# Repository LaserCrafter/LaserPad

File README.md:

# LaserPad
 Open Source replacement PCB for the Lightpad v2

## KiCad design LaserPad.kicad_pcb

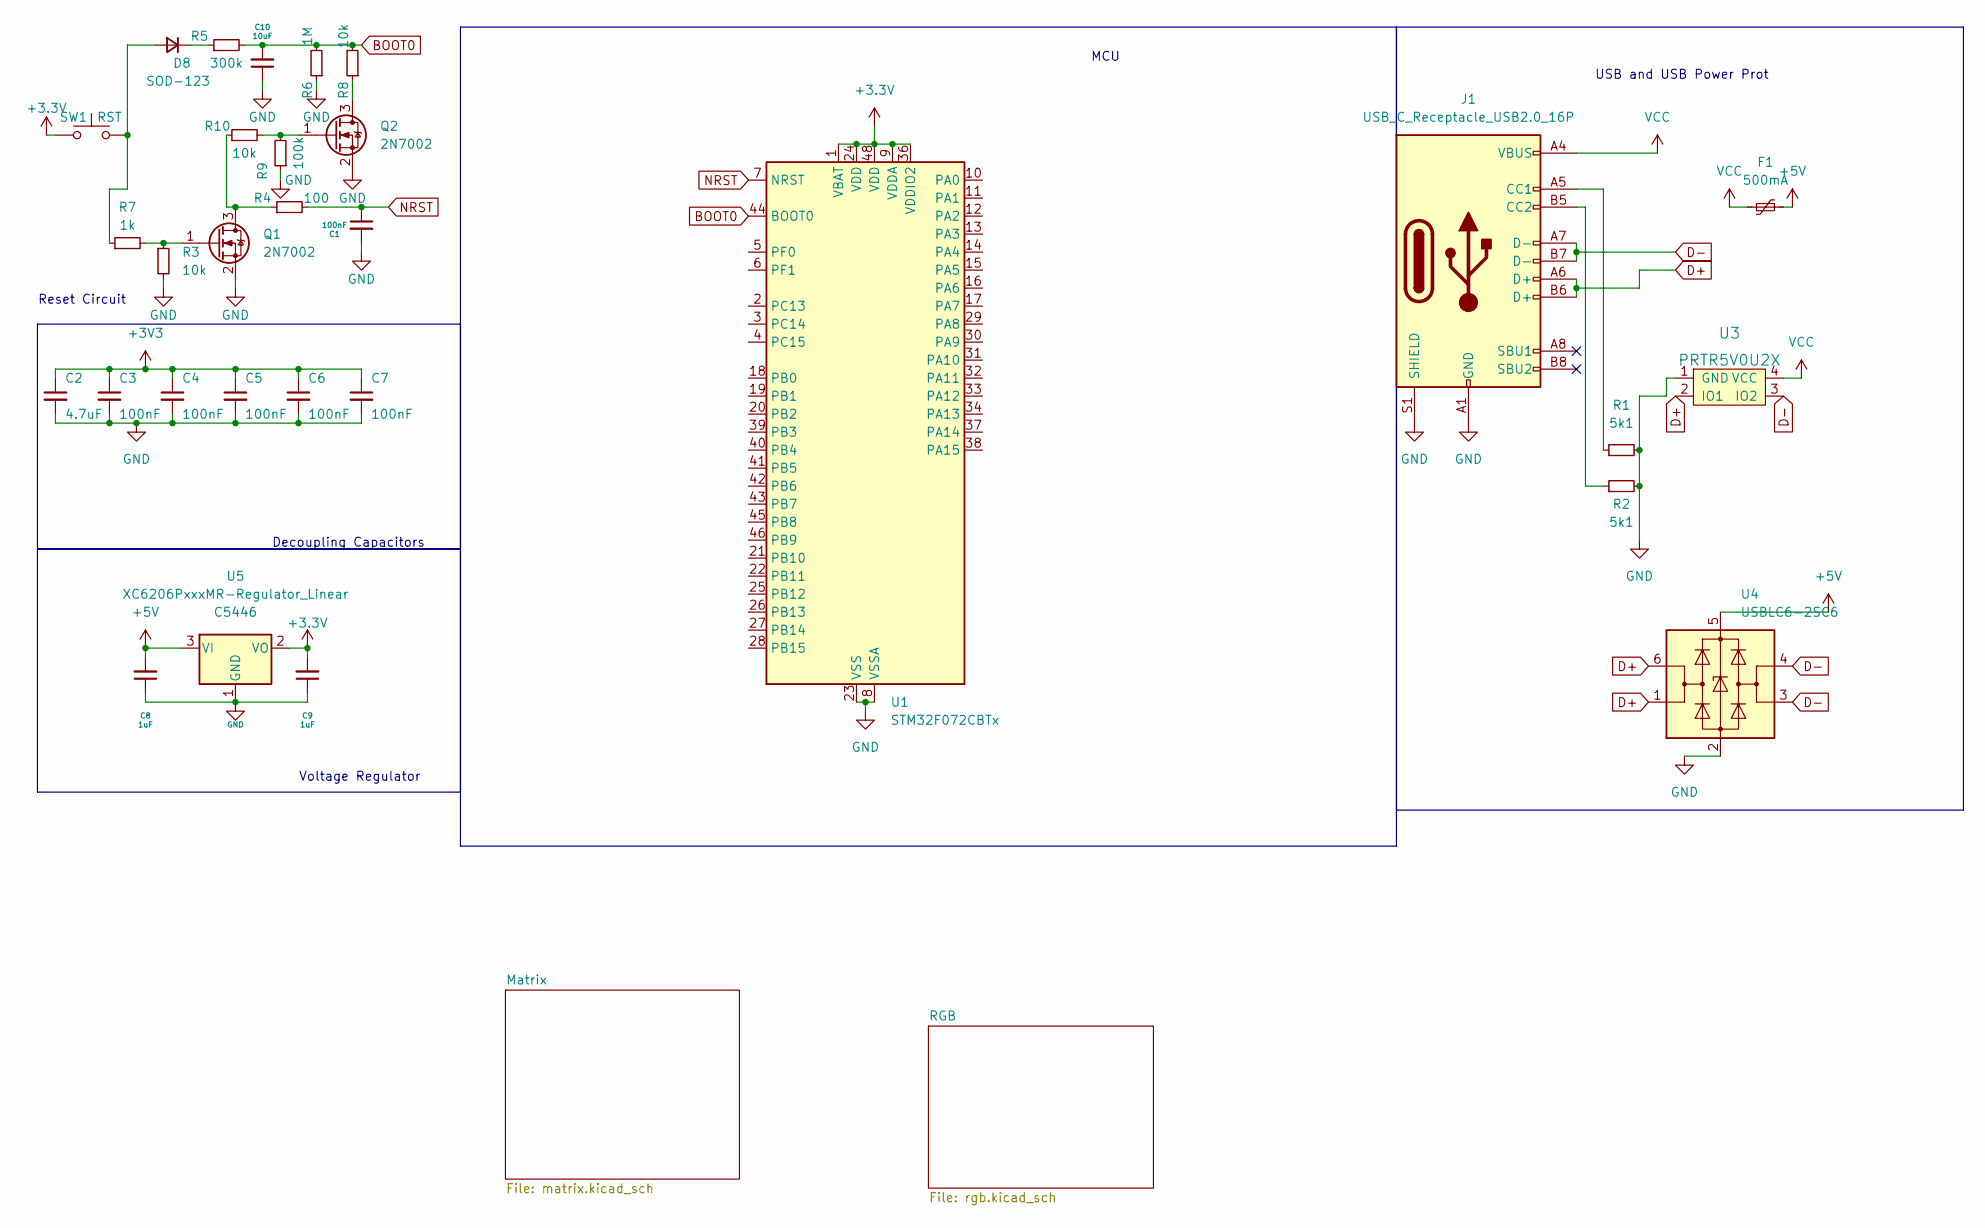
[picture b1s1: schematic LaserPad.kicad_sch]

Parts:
C1: 100nF; C_0402_1005Metric; LCSC C52923
C2: 4.7uF; C_0402_1005Metric; LCSC C52923
C3, C4, C5, C6, C7: 100nF; C_0402_1005Metric; LCSC C307331
C8, C9: 1uF; C_0402_1005Metric; LCSC C52923
C10: 10uF; C_0402_1005Metric; LCSC C52923
D8: SOD-123; D_SOD-123
F1: 500mA; Fuse_1206_3216Metric
J1: USB_C_Receptacle_USB2.0_16P; USB_C_Receptacle_HRO_TYPE-C-31-M-12
Q1, Q2: 2N7002; SOT-23
R1, R2: 5k1; R_0402_1005Metric
R3, R8, R10: 10k; R_0402_1005Metric
R4: 100; R_0402_1005Metric
R5: 300k; R_0402_1005Metric
R6: 1M; R_0402_1005Metric
R7: 1k; R_0402_1005Metric
R9: 100k; R_0402_1005Metric
SW1: RST; SW_SPST_SKQG_WithoutStem
U1: STM32F072CBTx; LQFP-48_7x7mm_P0.5mm
U3: PRTR5V0U2X; SOT143B
U4: USBLC6-2SC6; SOT-23-6
U5: XC6206PxxxMR-Regulator_Linear; SOT-23; LCSC C5446

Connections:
+3.3V: C9.2, SW1.1, U1.1 (VBAT), U1.9 (VDDA), U1.24 (VDD), U1.36 (VDDIO2), U1.48 (VDD), U5.2 (VO)
+3V3: C2.1, C3.1, C4.1, C5.1, C6.1, C7.1
+5V: C8.2, F1.1, F1.2, J1.A4 (VBUS), J1.A9 (VBUS), J1.B4 (VBUS), J1.B9 (VBUS), U3.4 (VCC), U4.5 (VBUS), U5.3 (VI); also elsewhere on the board
BOOT0: C10.2, R5.2, R6.2, R8.2, U1.44 (BOOT0)
D+: J1.A6 (D+), J1.B6 (D+), U3.2 (IO1), U4.1 (I/O1), U4.6 (I/O1)
D-: J1.A7 (D-), J1.B7 (D-), U3.3 (IO2), U4.3 (I/O2), U4.4 (I/O2)
GND: C1.2, C2.2, C3.2, C4.2, C5.2, C6.2, C7.2, C8.1, C9.1, C10.1, J1.A1 (GND), J1.A12 (GND), J1.B1 (GND), J1.B12 (GND), J1.S1 (SHIELD), Q1.2 (S), Q2.2 (S), R1.2, R2.2, R3.2, R6.1, R9.1, U1.8 (VSSA), U1.23 (VSS), U1.35 (VSS), U1.47 (VSS), U3.1 (GND), U4.2 (GND), U5.1 (GND); also elsewhere on the board
NRST: C1.1, R4.2, U1.7 (NRST)
unnamed: D8.2 (A), R7.1, SW1.2
unnamed: D8.1 (K), R5.1
unnamed: J1.A5 (CC1), R1.1
unnamed: J1.B5 (CC2), R2.1
unnamed: Q1.3 (D), R4.1, R10.1
unnamed: Q1.1 (G), R3.1, R7.2
unnamed: Q2.3 (D), R8.1
unnamed: Q2.1 (G), R9.2, R10.2

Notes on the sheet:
Voltage Regulator
MCU
Decoupling Capacitors
Reset Circuit
USB and USB Power Prot

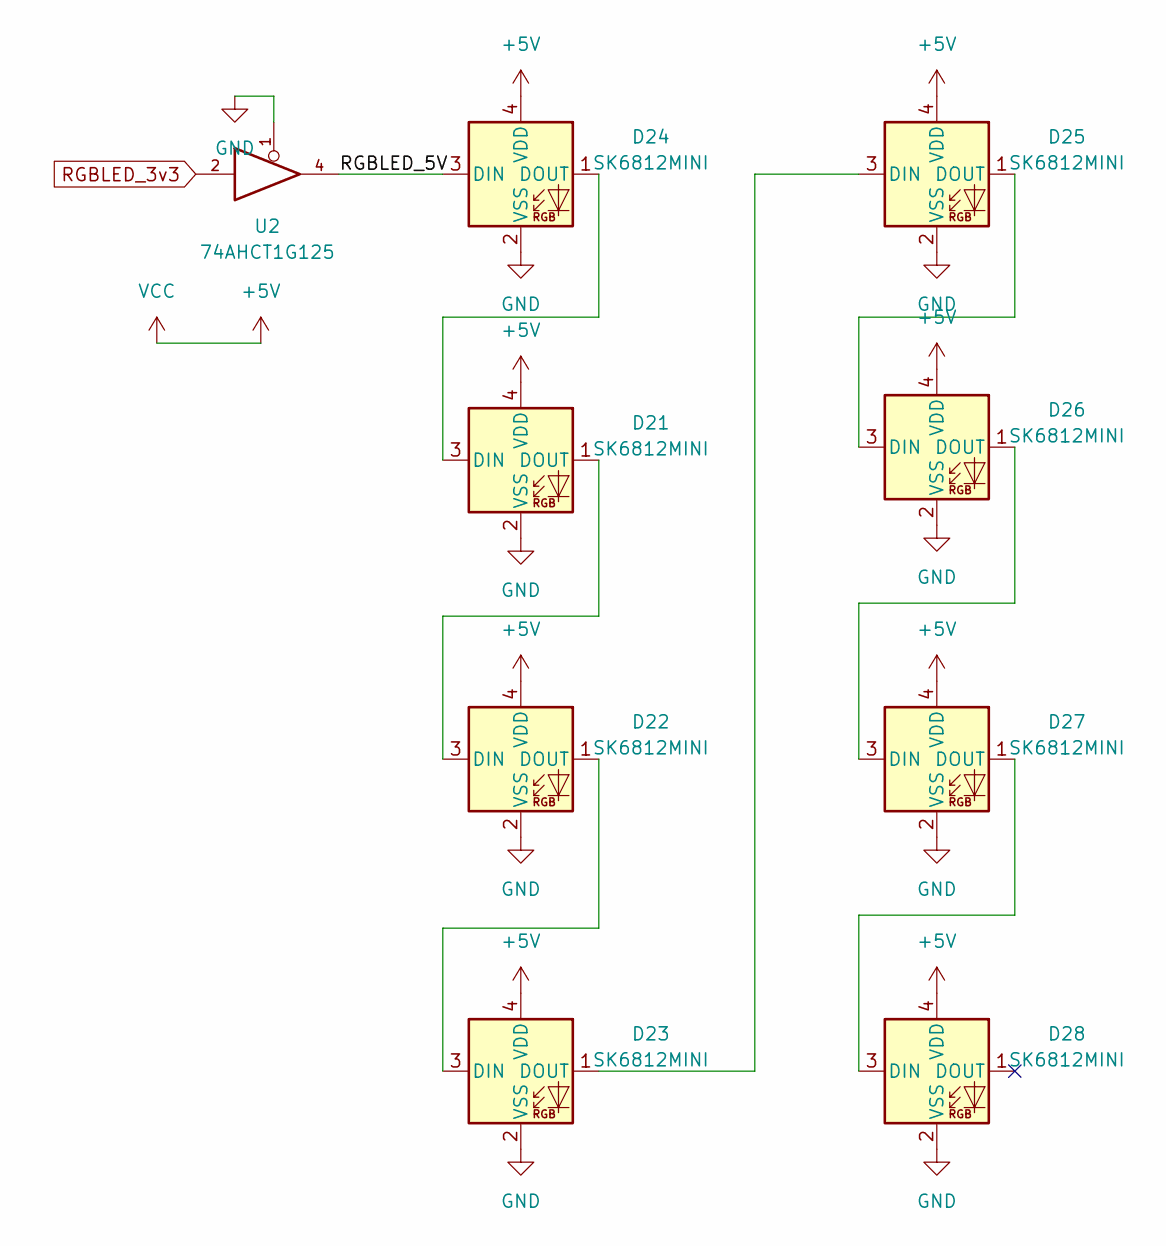
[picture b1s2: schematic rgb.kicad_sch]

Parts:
D21, D22, D23, D24, D25, D26, D27, D28: SK6812MINI; LED_SK6812MINI_PLCC4_3.5x3.5mm_P1.75mm
U2: 74AHCT1G125; SOT-23-5

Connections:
+5V: D21.4 (VDD), D22.4 (VDD), D23.4 (VDD), D24.4 (VDD), D25.4 (VDD), D26.4 (VDD), D27.4 (VDD), D28.4 (VDD), U2.5 (VCC); also elsewhere on the board
/RGB/RGBLED_5V: D24.3 (DIN), U2.4
GND: D21.2 (VSS), D22.2 (VSS), D23.2 (VSS), D24.2 (VSS), D25.2 (VSS), D26.2 (VSS), D27.2 (VSS), D28.2 (VSS), U2.1, U2.3 (GND); also elsewhere on the board
unnamed: D21.3 (DIN), D24.1 (DOUT)
unnamed: D21.1 (DOUT), D22.3 (DIN)
unnamed: D22.1 (DOUT), D23.3 (DIN)
unnamed: D23.1 (DOUT), D25.3 (DIN)
unnamed: D25.1 (DOUT), D26.3 (DIN)
unnamed: D26.1 (DOUT), D27.3 (DIN)
unnamed: D27.1 (DOUT), D28.3 (DIN)
RGBLED_3v3: U2.2

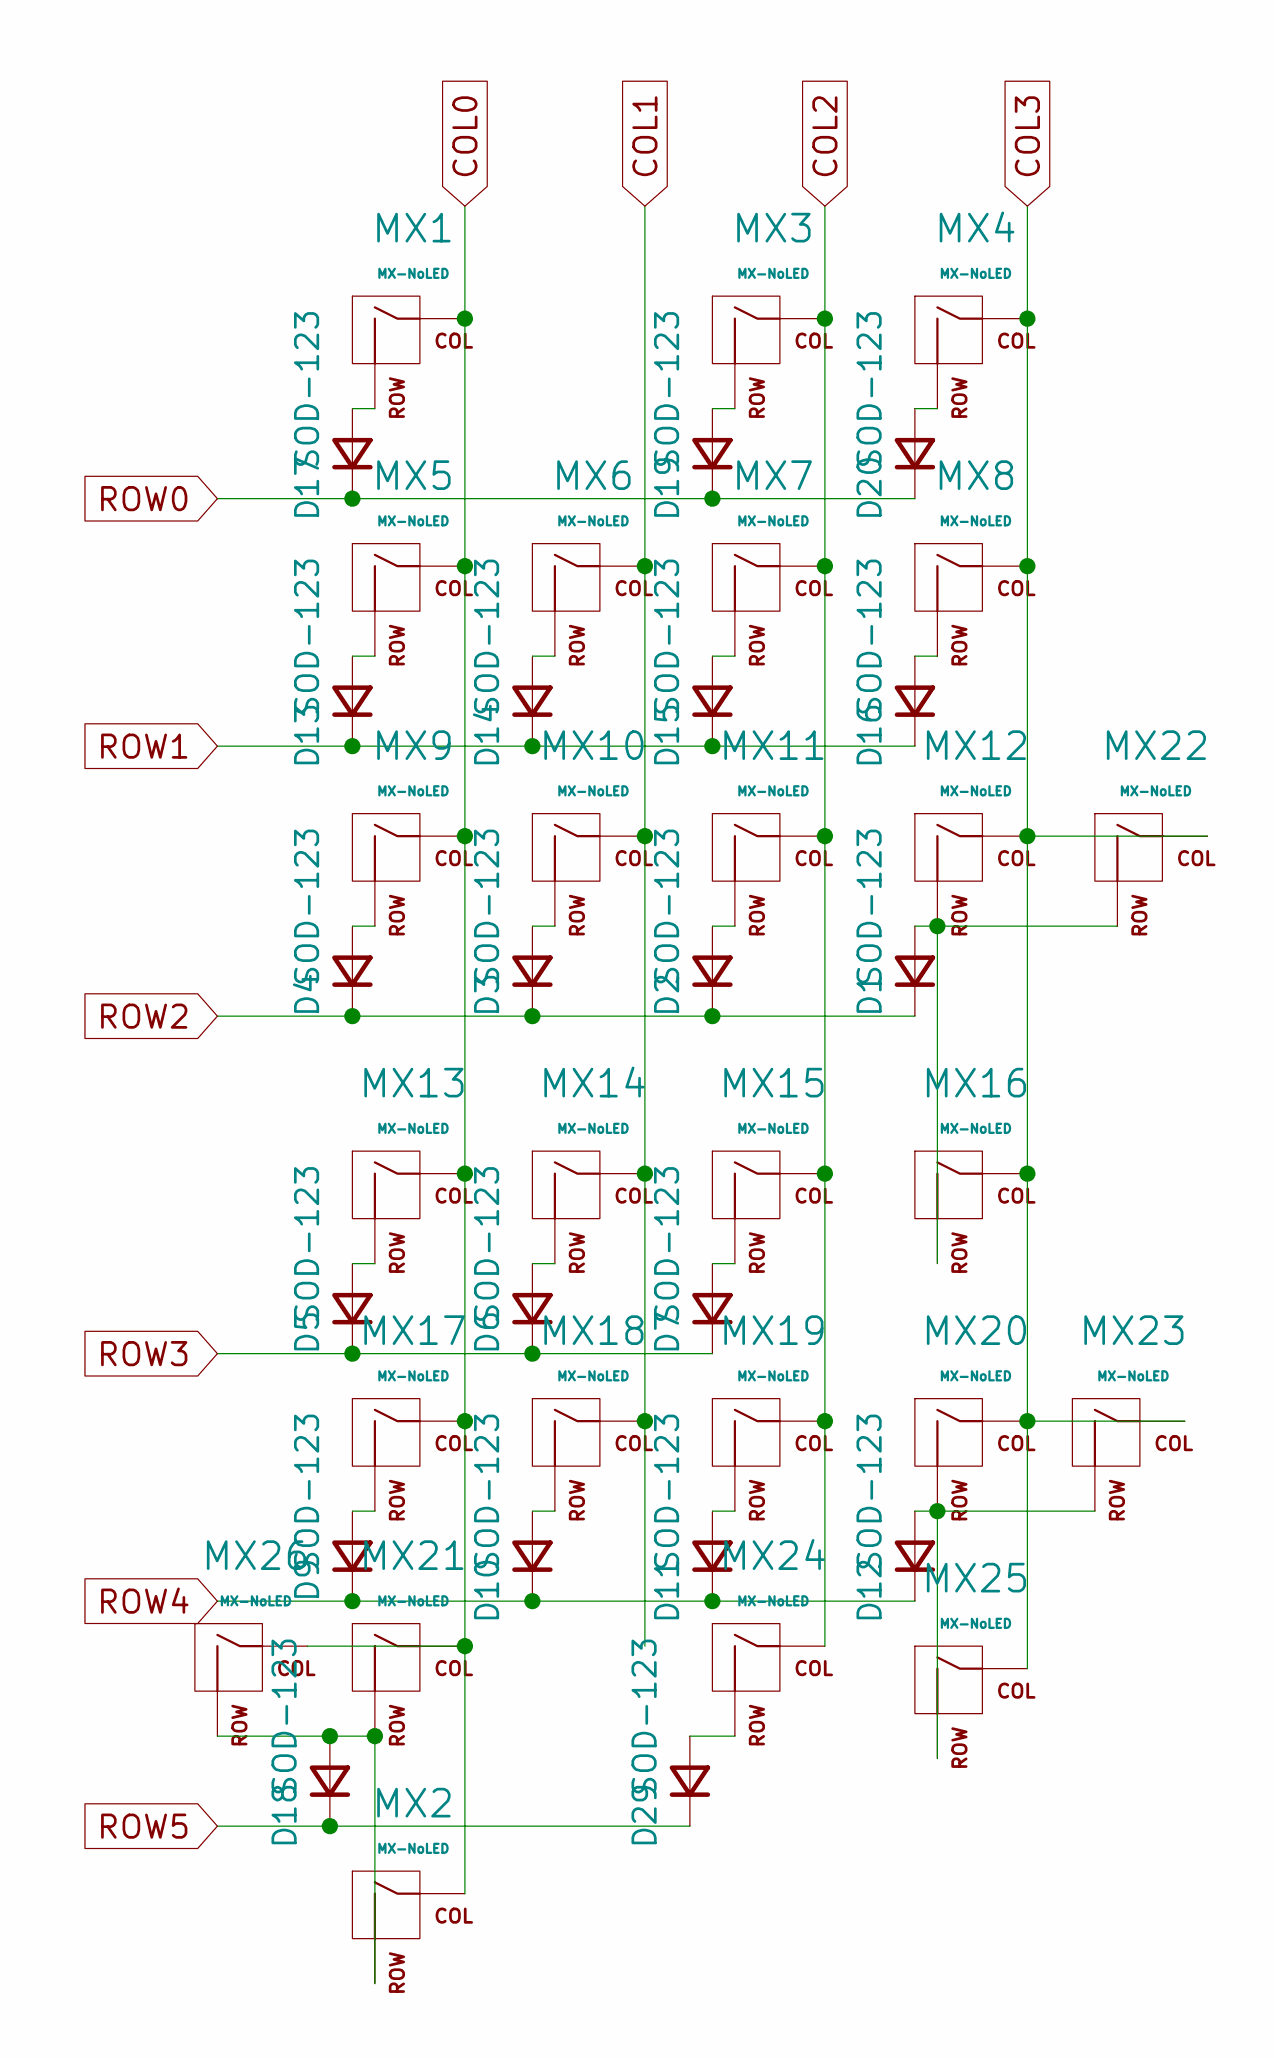
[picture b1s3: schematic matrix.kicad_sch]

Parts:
D1, D2, D3, D4, D5, D6, D7, D9, D10, D11, D12, D13, D14, D15, D16, D17, D18, D19, D20, D29: SOD-123; D_SOD-123
MX1, MX2, MX3, MX4, MX5, MX6, MX7, MX8, MX9, MX10, MX11, MX12, MX13, MX14, MX15, MX16, MX17, MX18, MX19, MX20, MX24, MX25, MX26: MX-NoLED; MXOnly-1U-NoLED
MX21, MX22, MX23: MX-NoLED; MXOnly-2U-ReversedStabilizers-NoLED

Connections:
COL0: MX1.1 (COL), MX2.1 (COL), MX5.1 (COL), MX9.1 (COL), MX13.1 (COL), MX17.1 (COL), MX21.1 (COL), MX26.1 (COL)
COL1: MX6.1 (COL), MX10.1 (COL), MX14.1 (COL), MX18.1 (COL)
COL2: MX3.1 (COL), MX7.1 (COL), MX11.1 (COL), MX15.1 (COL), MX19.1 (COL), MX24.1 (COL)
COL3: MX4.1 (COL), MX8.1 (COL), MX12.1 (COL), MX16.1 (COL), MX20.1 (COL), MX22.1 (COL), MX23.1 (COL), MX25.1 (COL)
unnamed: D1.2 (A), MX12.2 (ROW), MX16.2 (ROW), MX22.2 (ROW)
unnamed: D2.2 (A), MX11.2 (ROW)
unnamed: D3.2 (A), MX10.2 (ROW)
unnamed: D4.2 (A), MX9.2 (ROW)
unnamed: D5.2 (A), MX13.2 (ROW)
unnamed: D6.2 (A), MX14.2 (ROW)
unnamed: D7.2 (A), MX15.2 (ROW)
unnamed: D9.2 (A), MX17.2 (ROW)
unnamed: D10.2 (A), MX18.2 (ROW)
unnamed: D11.2 (A), MX19.2 (ROW)
unnamed: D12.2 (A), MX20.2 (ROW), MX23.2 (ROW), MX25.2 (ROW)
unnamed: D13.2 (A), MX5.2 (ROW)
unnamed: D14.2 (A), MX6.2 (ROW)
unnamed: D15.2 (A), MX7.2 (ROW)
unnamed: D16.2 (A), MX8.2 (ROW)
unnamed: D17.2 (A), MX1.2 (ROW)
unnamed: D18.2 (A), MX2.2 (ROW), MX21.2 (ROW), MX26.2 (ROW)
unnamed: D19.2 (A), MX3.2 (ROW)
unnamed: D20.2 (A), MX4.2 (ROW)
unnamed: D29.2 (A), MX24.2 (ROW)
ROW0: D17.1 (K), D19.1 (K), D20.1 (K)
ROW1: D13.1 (K), D14.1 (K), D15.1 (K), D16.1 (K)
ROW2: D1.1 (K), D2.1 (K), D3.1 (K), D4.1 (K)
ROW3: D5.1 (K), D6.1 (K), D7.1 (K)
ROW4: D9.1 (K), D10.1 (K), D11.1 (K), D12.1 (K)
ROW5: D18.1 (K), D29.1 (K)

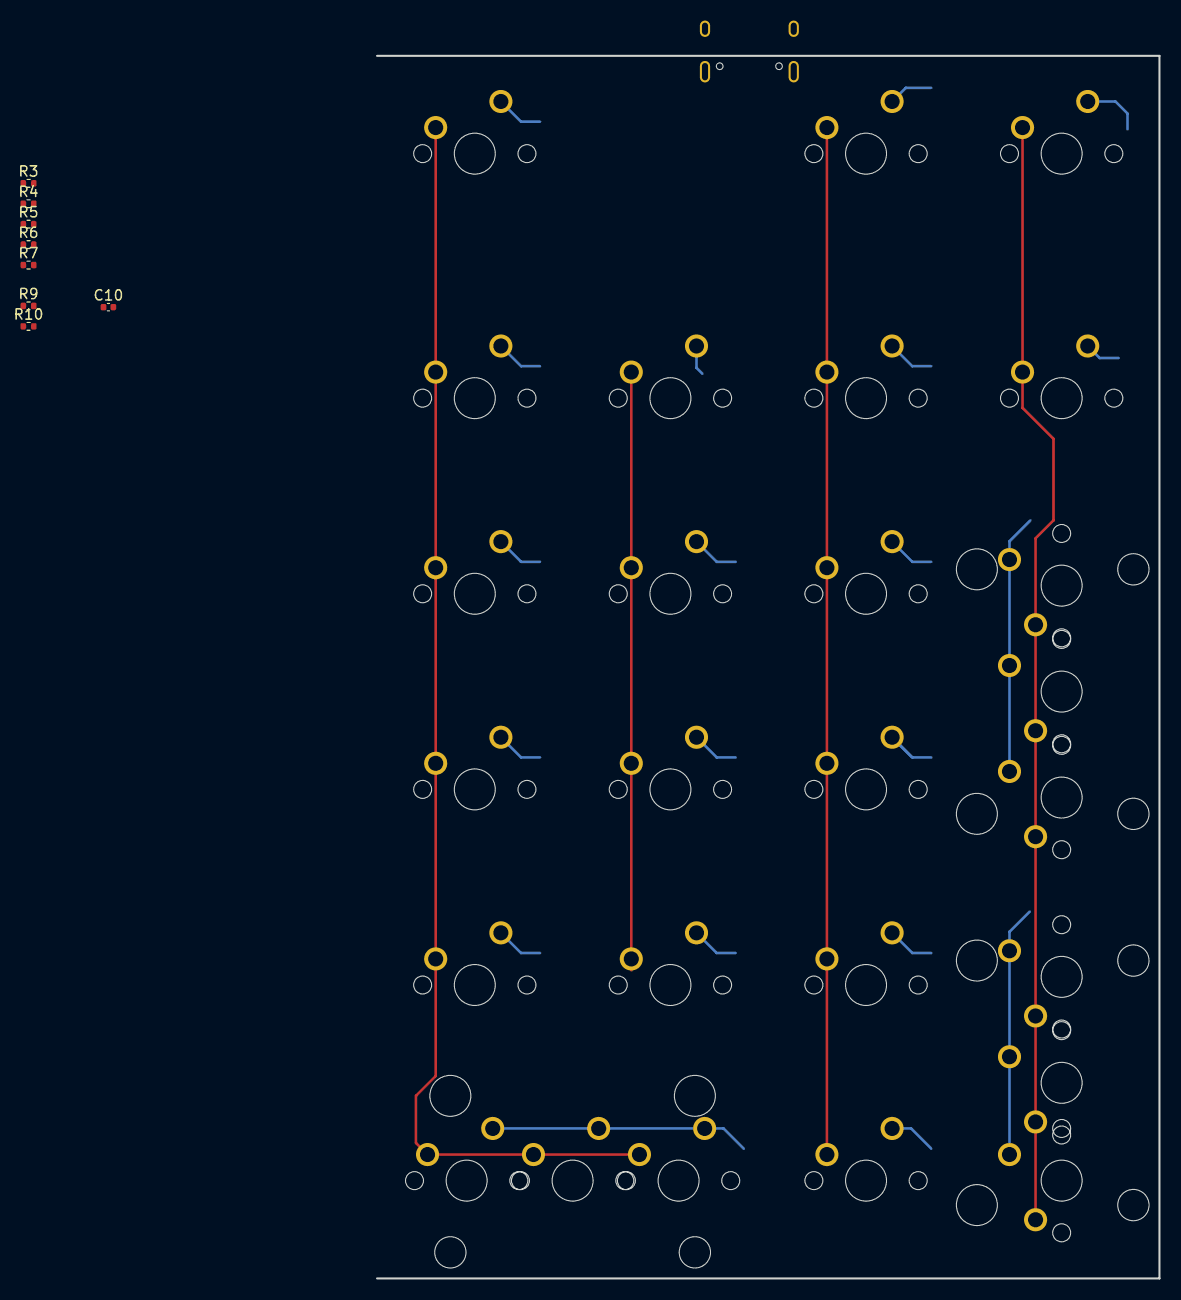
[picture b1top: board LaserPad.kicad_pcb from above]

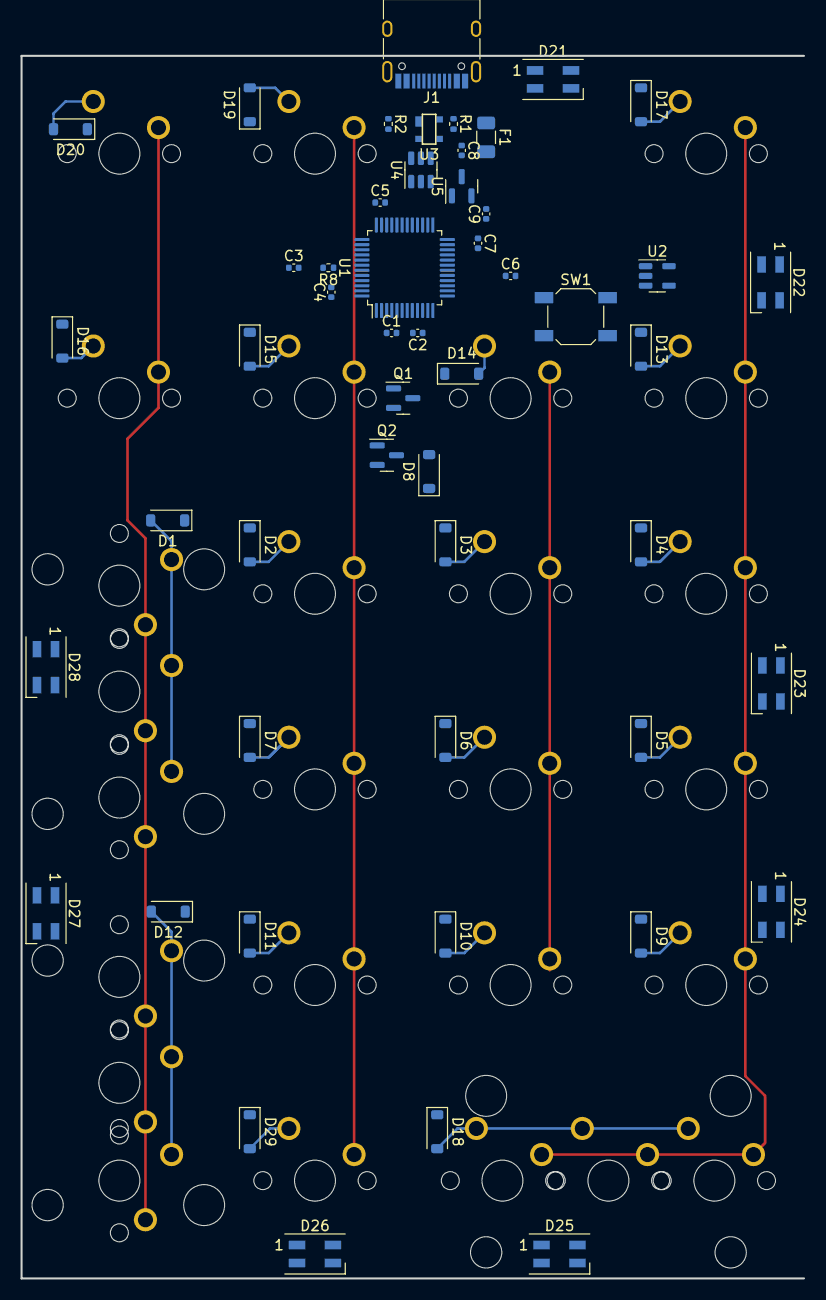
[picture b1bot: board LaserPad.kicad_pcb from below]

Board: 2 copper layers, 76.2 x 119.1 mm, 85 parts (51 on the bottom side), 54 nets.

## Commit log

2024-01-30 Initialized Project
2024-01-30 added submodules curteousy of ai03 and changed footprint and symbol libraries
2024-01-30 Created 2 schematics for rgb and the switch matrix
2024-01-30 Created matrix.
2024-01-30 made columns and rows
2024-01-30 creating led matrix.
2024-01-30 Wiring LED matrix
2024-01-31 Selected MCU and wired up RGB Led Underglow
2024-01-31 no changes since.
2024-02-01 Routed RGB LED Wires
2024-02-01 Switched LEDS to SK6812 mini for space constraints
2024-02-01 Wired USB-C connector in schematic.
2024-02-01 added usb power protection
2024-02-01 did a little organization :/
2024-02-02 idk lol
2024-02-08 Changed MCU to STM32, Redone footprints for USB, keyswitches, LEDS, and other things, and configured PCB Editor for general switch placement
2024-02-08 Working on fixing up the footprints for some components
2024-02-08 updated pcb files, wired up a new usb connector in the schematic, cleaned up a couple of wiring within the schematic
2024-02-13 Placed Components and in the process of routing
2024-02-13 Almost done placing components into PCB
2024-02-20 many changes
2024-02-22 Changed reset circuit into something that will hopefully take up less space on pcb
2024-02-23 Changed around a couple of objects for new reset circuit
2024-03-05 Changed reset circuit yet again :/
